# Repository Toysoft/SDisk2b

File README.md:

# SDisk2 - Simplified

Disk II flopy drive emulator for Apple 2 computers

Objective. an Open Source Disk II floppy Disk emulator that is easy to make.  
See readme in firmware and PCB section for related info.

## Changes

* 27Mhz Xtal.
* OLED only. All LCD and Nokia LCD codes have been removed.
* All Screen rotation code removed.
* Buttons re-arranged

## To-do

1. Better documentaion of the code.

This project will be migrated to an ESP32 based SDISKII.
<https://github.com/terenceang/sdisk2esp>

## Authors

* (c) 2010 Koichi NISHIDA <tulip-house@msf.biglobe.ne.jp>
* (c) 2012 Victor Trucco
* (c) 2012 Fábio Belavenuto
* (c) 2015 Alexandre Suaide
* (c) 2022 Terence Ang

## License

This work is released under the version 3 of the GNU General Public License.

'''NOTE:'''
The current legal status of this code is uncertain.

Fábio and Alexandre have published files with a header that references the version 3 of the GNU General Public License, but it is not clear yet what's the licensing chosen by the original author, Koichi Nishida.

This repository will be updated once the actual licensing info is clarified by the authors.

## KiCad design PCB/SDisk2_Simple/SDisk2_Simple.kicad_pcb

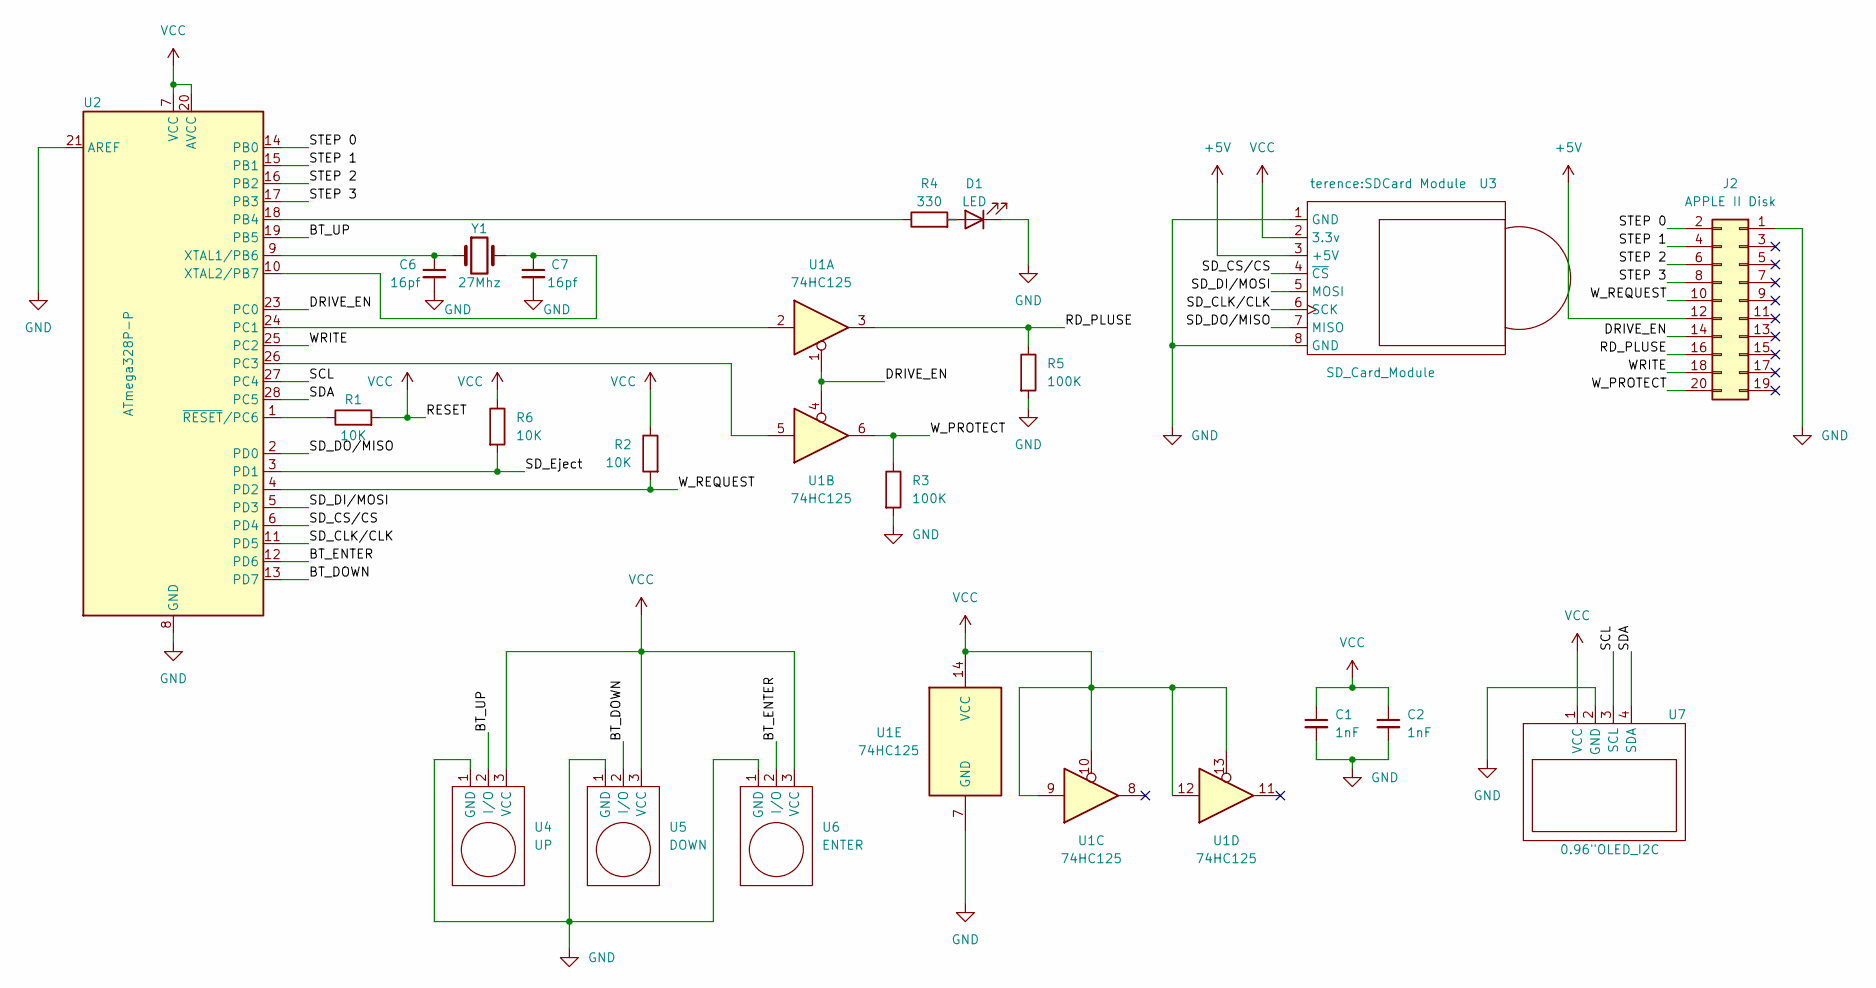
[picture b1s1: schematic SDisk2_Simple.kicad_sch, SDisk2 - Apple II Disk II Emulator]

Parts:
C1, C2: 1nF; C_0805_2012Metric
C6, C7: 16pf; C_0805_2012Metric
D1: LED; LED_0805_2012Metric
J2: APPLE II Disk; IDC-Header_2x10_P2.54mm_Vertical
R1, R2, R6: 10K; R_0805_2012Metric
R3, R5: 100K; R_0805_2012Metric
R4: 330; R_0805_2012Metric
U1: 74HC125; DIP-14_W7.62mm
U2: ATmega328P-P; DIP-28_W7.62mm
U3: SD_Card_Module; SDCard Module
U4: UP; TP223
U5: DOWN; TP223
U6: ENTER; TP223
U7: 0.96"OLED_I2C; 0.96OLED I2C
Y1: 27Mhz; Crystal_HC49-U_Vertical

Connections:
+5V: J2.12, U3.3 (+5V)
/BT_DOWN: U2.13 (PD7), U5.2 (I/O)
/BT_ENTER: U2.12 (PD6), U6.2 (I/O)
/BT_UP: U2.19 (PB5), U4.2 (I/O)
/DRIVE_EN: J2.14, U1.1, U1.4, U2.23 (PC0)
/RD_PLUSE: J2.16, R5.1, U1.3
/SCL: U2.27 (PC4), U7.3 (SCL)
/SDA: U2.28 (PC5), U7.4 (SDA)
/SD_CLK/CLK: U2.11 (PD5), U3.6 (SCK)
/SD_CS/CS: U2.6 (PD4), U3.4 (~CS)
/SD_DI/MOSI: U2.5 (PD3), U3.5 (MOSI)
/SD_DO/MISO: U2.2 (PD0), U3.7 (MISO)
/SD_Eject: R6.2, U2.3 (PD1)
/STEP 0: J2.2, U2.14 (PB0)
/STEP 1: J2.4, U2.15 (PB1)
/STEP 2: J2.6, U2.16 (PB2)
/STEP 3: J2.8, U2.17 (PB3)
/WRITE: J2.18, U2.25 (PC2)
/W_PROTECT: J2.20, R3.1, U1.6
/W_REQUEST: J2.10, R2.2, U2.4 (PD2)
GND: C1.2, C2.2, C6.2, C7.2, D1.1 (K), J2.1, R3.2, R5.2, U1.7 (GND), U2.8 (GND), U2.21 (AREF), U2.22 (GND), U3.1 (GND), U3.8 (GND), U4.1 (GND), U5.1 (GND), U6.1 (GND), U7.2 (GND)
unnamed: C6.1, U2.9 (XTAL1/PB6), Y1.1
unnamed: C7.1, U2.10 (XTAL2/PB7), Y1.2
unnamed: D1.2 (A), R4.2
unnamed: R1.1, U2.1 (~RESET/PC6)
unnamed: R4.1, U2.18 (PB4)
unnamed: U1.2, U2.24 (PC1)
unnamed: U1.5, U2.26 (PC3)
VCC: C1.1, C2.1, R1.2, R2.1, R6.1, U1.9, U1.10, U1.12, U1.13, U1.14 (VCC), U2.7 (VCC), U2.20 (AVCC), U3.2 (3.3v), U4.3 (VCC), U5.3 (VCC), U6.3 (VCC), U7.1 (VCC)

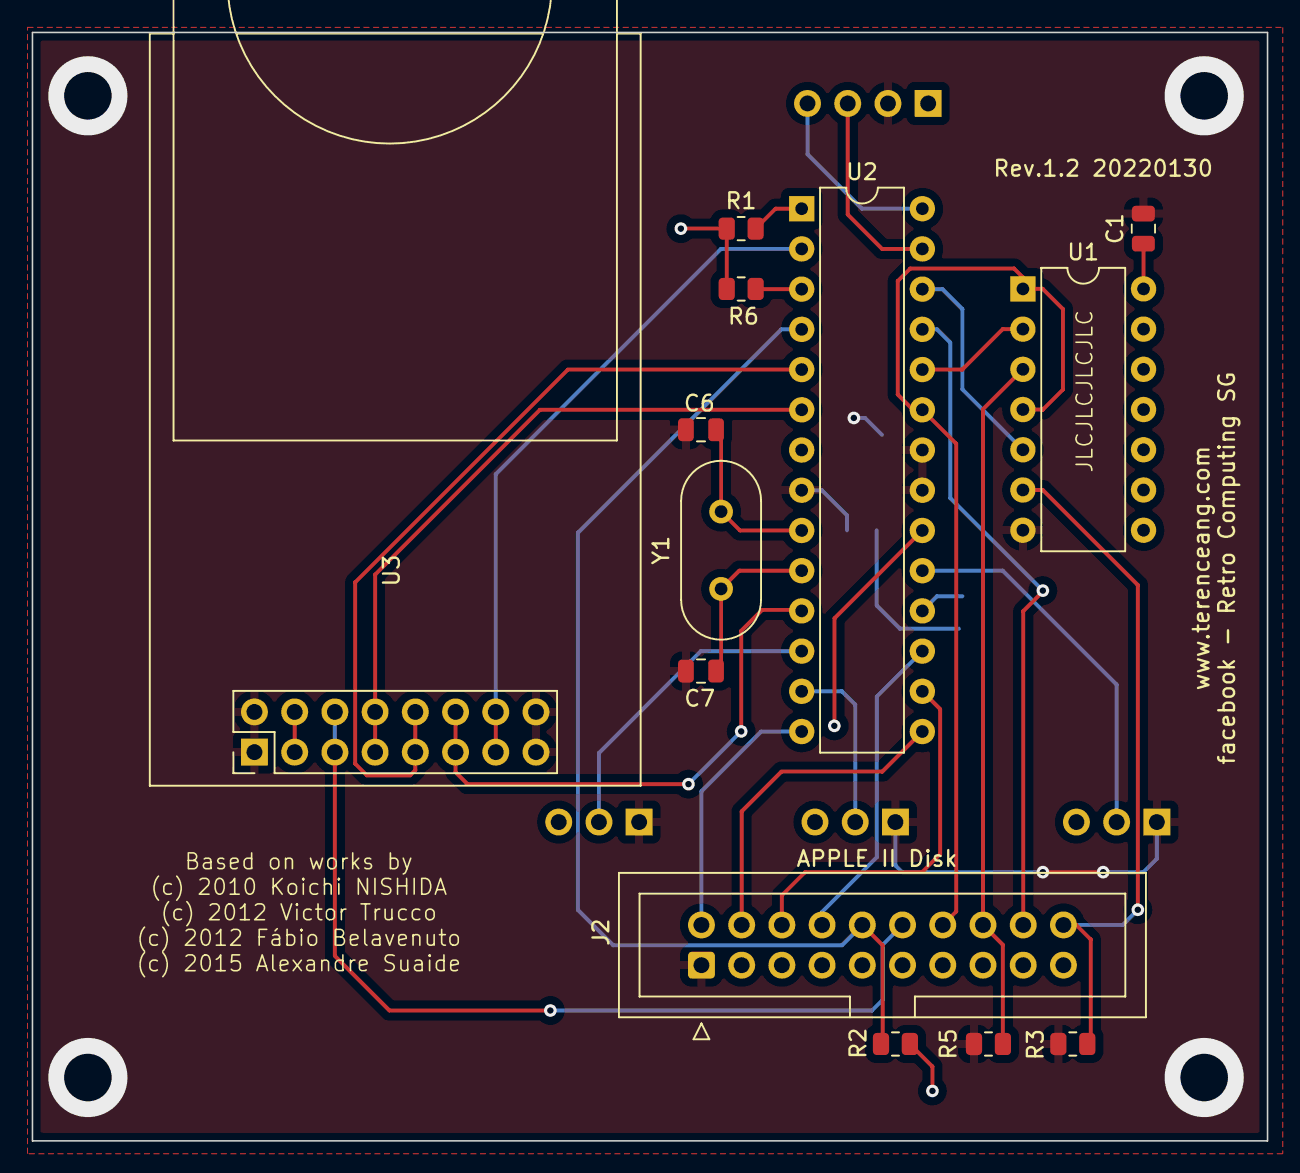
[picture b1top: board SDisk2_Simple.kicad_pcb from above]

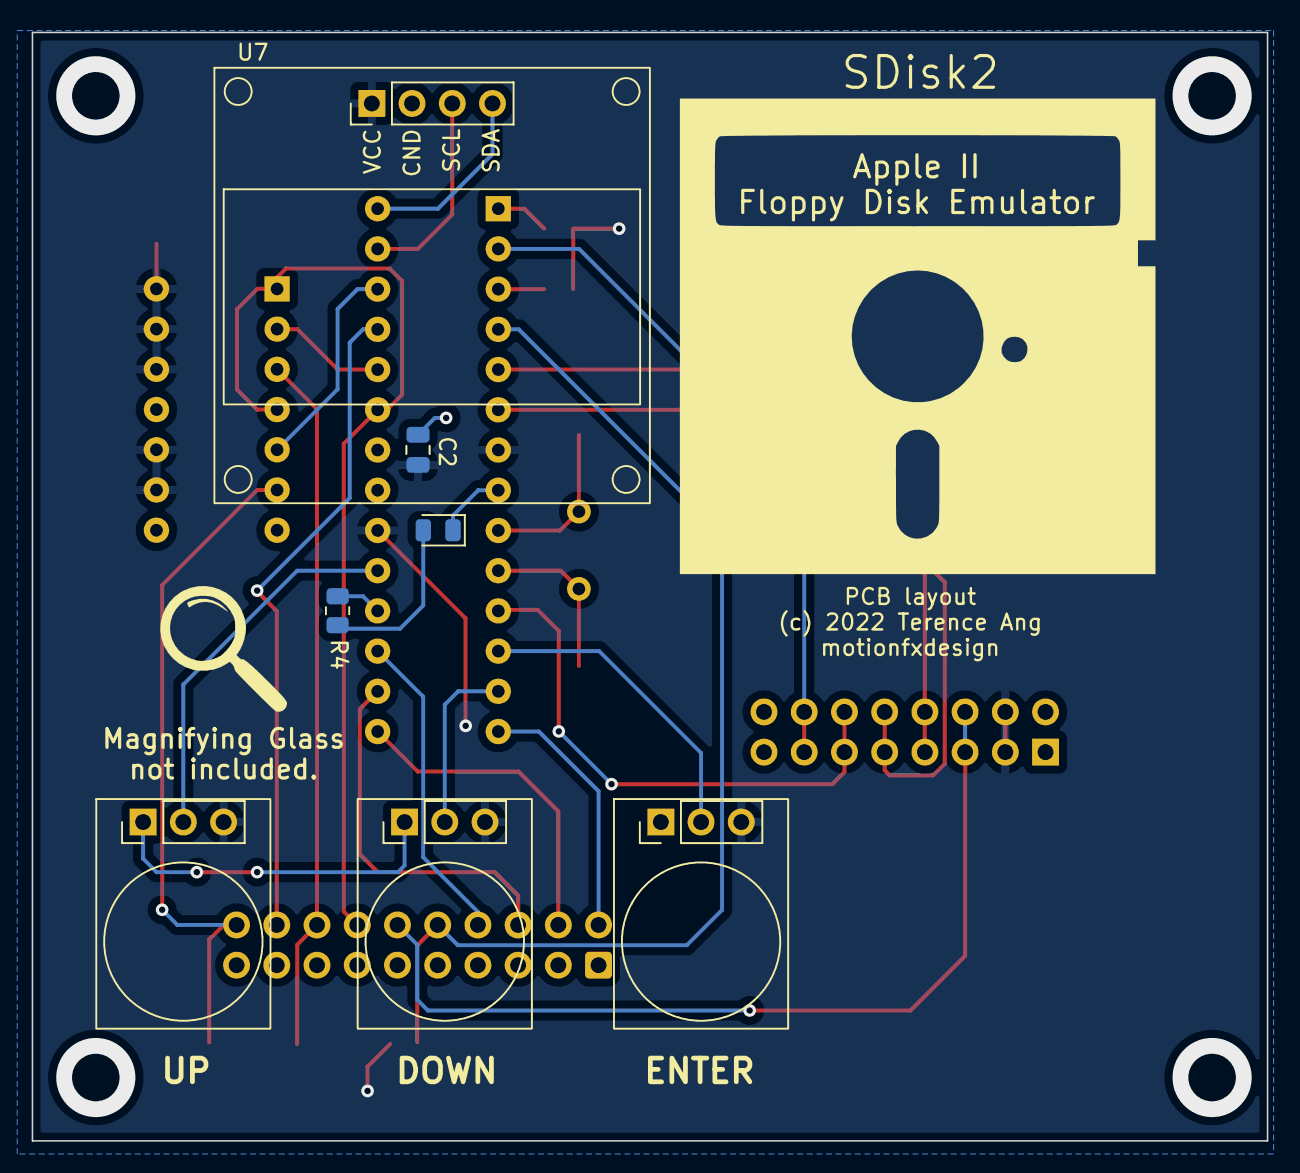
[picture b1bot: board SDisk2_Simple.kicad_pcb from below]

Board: 2 copper layers, 78.0 x 70.0 mm, 20 parts (7 on the bottom side), 29 nets.

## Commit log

2022-01-26 clean up
2022-01-27 PCB initial
2022-03-02 Simple SDISK II
2022-03-02 cleanup
2022-03-02 more info

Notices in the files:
PCB/SDisk2_Simple/SDisk2_Simple.kicad_pcb:
Based on works by
(c) 2010 Koichi NISHIDA
(c) 2012 Victor Trucco
PCB/SDisk2_Simple/SDisk2_Simple.kicad_sch:
Based on original works from (c) 2010 Koichi NISHIDA tulip-house@msf.biglobe.ne.jp
